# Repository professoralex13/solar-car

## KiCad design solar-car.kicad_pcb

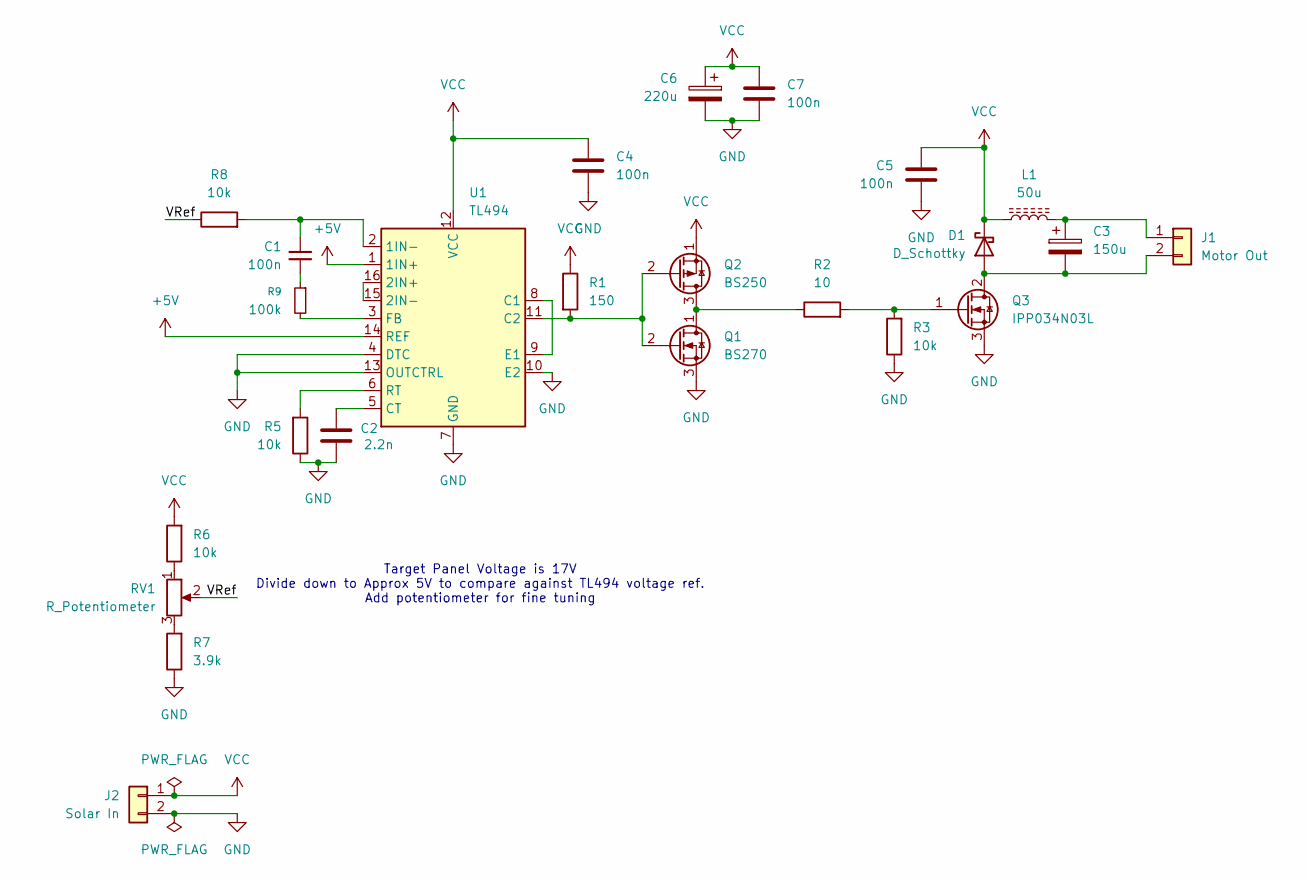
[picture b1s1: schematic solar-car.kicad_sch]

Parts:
C1, C4, C5: 100n; C_Disc_D5.0mm_W2.5mm_P5.00mm
C2: 2.2n; C_Disc_D5.0mm_W2.5mm_P5.00mm
C3: 150u; CP_Radial_D6.3mm_P2.50mm
C6: 220u; CP_Radial_D6.3mm_P2.50mm
C7: 100n; CP_Radial_D6.3mm_P2.50mm
D1: D_Schottky; D_DO-41_SOD81_P10.16mm_Horizontal
J1: Motor Out; PinHeader_1x02_P2.54mm_Vertical
J2: Solar In; PinHeader_1x02_P2.54mm_Vertical
L1: 50u; PinHeader_1x02_P2.54mm_Vertical
Q1: BS270; TO-92_Wide
Q2: BS250; TO-92_Wide
Q3: IPP034N03L; TO-220-3_Horizontal_TabDown
R1: 150; R_Axial_DIN0207_L6.3mm_D2.5mm_P7.62mm_Horizontal
R2: 10; R_Axial_DIN0207_L6.3mm_D2.5mm_P7.62mm_Horizontal
R3, R5, R6, R8: 10k; R_Axial_DIN0207_L6.3mm_D2.5mm_P7.62mm_Horizontal
R7: 3.9k; R_Axial_DIN0207_L6.3mm_D2.5mm_P7.62mm_Horizontal
R9: 100k; R_Axial_DIN0207_L6.3mm_D2.5mm_P7.62mm_Horizontal
RV1: R_Potentiometer; Potentiometer_Bourns_3299P_Horizontal
U1: TL494; DIP-16_W7.62mm

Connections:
+5V: U1.1 (1IN+), U1.14 (REF)
/VRef: R8.1, RV1.2
GND: C2.2, C4.2, C5.2, C6.2, C7.2, J2.2, Q1.3 (S), Q3.3 (S), R3.1, R5.1, R7.1, U1.4 (DTC), U1.7 (GND), U1.10 (E2), U1.13 (OUTCTRL)
unnamed: C1.2, R9.1
unnamed: C3.2, D1.2 (A), J1.2, Q3.2 (D)
unnamed: C3.1, J1.1, L1.2
unnamed: Q1.1 (D), Q2.3 (D), R2.1
unnamed: Q1.2 (G), Q2.2 (G), R1.2, U1.11 (C2)
unnamed: Q3.1 (G), R2.2, R3.2
unnamed: R6.1, RV1.1
unnamed: R7.2, RV1.3
unnamed: C1.1, R8.2, U1.2 (1IN-)
unnamed: U1.15 (2IN-), U1.16 (2IN+)
unnamed: U1.8 (C1), U1.9 (E1)
unnamed: C2.1, U1.5 (CT)
unnamed: R9.2, U1.3 (FB)
unnamed: R5.2, U1.6 (RT)
VCC: C4.1, C5.1, C6.1, C7.1, D1.1 (K), J2.1, L1.1, Q2.1 (S), R1.1, R6.2, U1.12 (VCC)

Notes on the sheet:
Target Panel Voltage is 17V Divide down to Approx 5V to compare against TL494 voltage ref. Add potentiometer for fine tuning

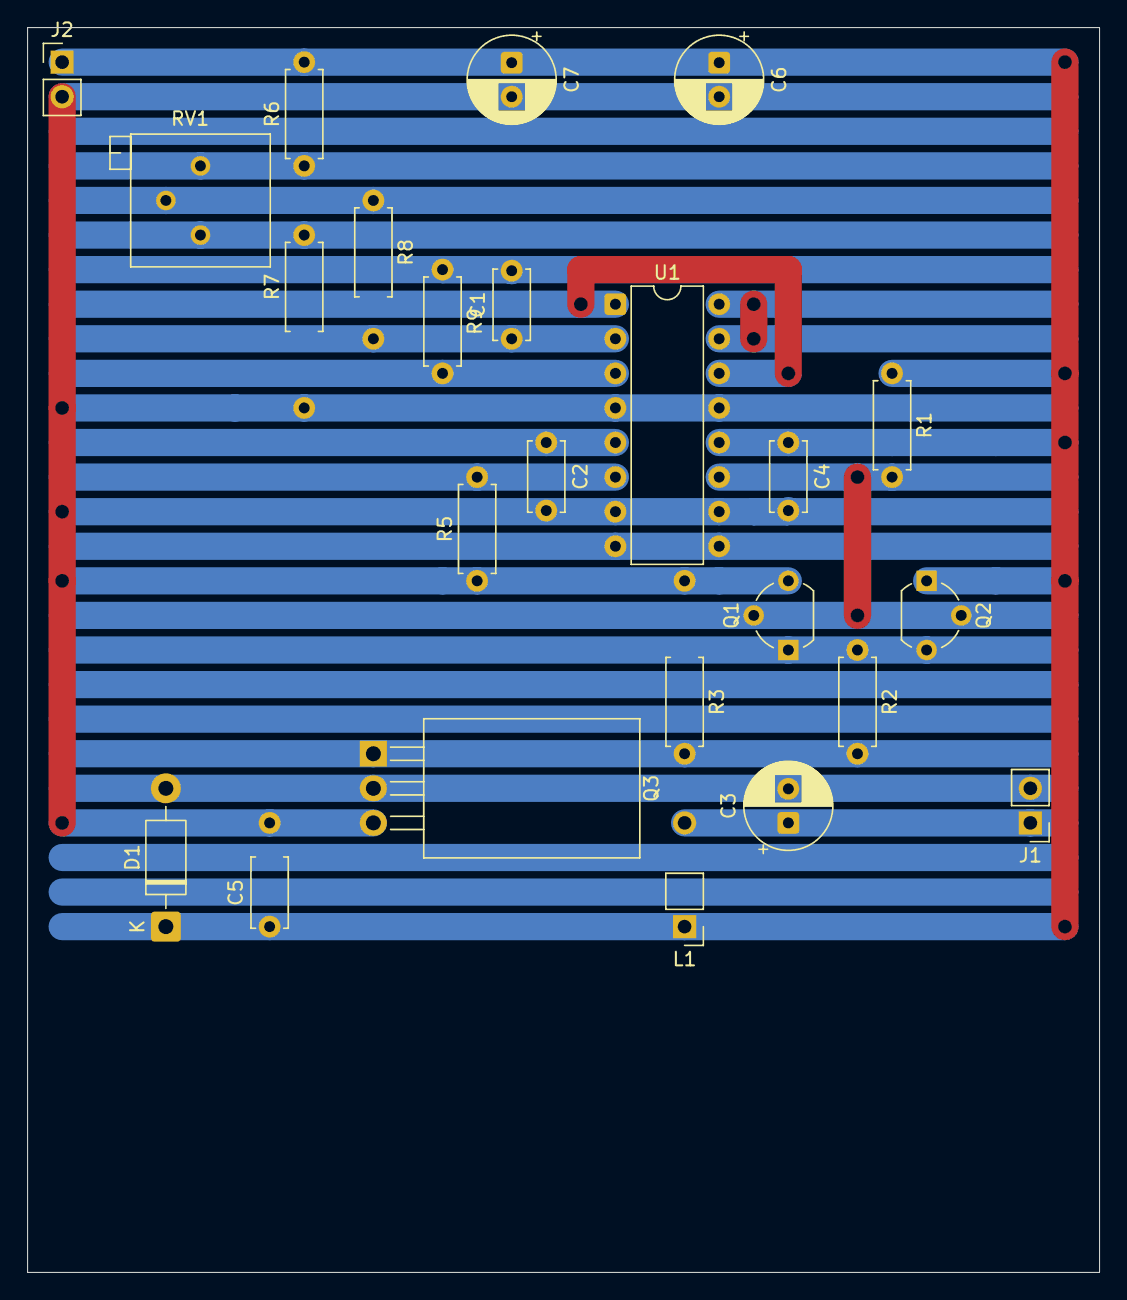
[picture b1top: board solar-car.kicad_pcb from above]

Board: 2 copper layers, 78.7 x 91.4 mm, 24 parts (0 on the bottom side), 18 nets.
